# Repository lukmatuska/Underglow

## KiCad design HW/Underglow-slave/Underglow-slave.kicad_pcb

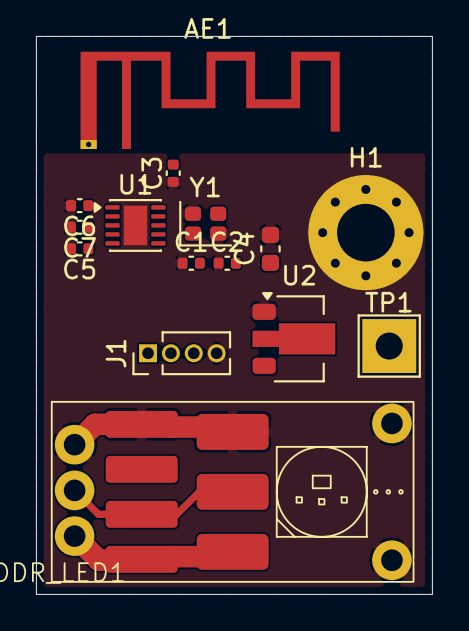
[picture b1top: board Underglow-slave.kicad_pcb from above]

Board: 2 copper layers, 22.0 x 31.0 mm, 15 parts (0 on the bottom side), 10 nets, no tracks yet.

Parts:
ADDR_LED1: Addressable_led_adapter_10mm
AE1: Antenna; Texas_SWRA117D_2.4GHz_Right
C1, C2, C3: DNP; C_0402_1005Metric
C4: 1u 25V; C_0603_1608Metric
C5: 1u; C_0402_1005Metric
C6: 2.2u; C_0402_1005Metric
C7: 100n; C_0402_1005Metric
H1: GND screw; MountingHole_3.2mm_M3_Pad_Via
J1: Debug_header; PinHeader_1x04_P1.27mm_Vertical
TP1: +12V in; TestPoint_THTPad_3.0x3.0mm_Drill1.5mm
U1: CH572Q; DFN-10-1EP_2.6x2.6mm_P0.5mm_EP1.3x2.2mm
U2: HT7550-1; SOT-89-3
Y1: 32MHz 8pF; Crystal_SMD_2016-4Pin_2.0x1.6mm

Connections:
+3.3V: C6.1, C7.1, J1.1, U1.1 (VDD33)
+5V: C5.1, U1.2 (V5), U2.3
+12V: ADDR_LED1.1 (VDD), C4.1, TP1.1, U2.2
/LED_RGB: ADDR_LED1.2 (DIN), U1.5 (PA7)
/SWCLK: J1.3, U1.4 (PA1)
/SWDIO: J1.2, U1.3 (PA0)
/XIN: C1.2, U1.9 (XI), Y1.1
/XOUT: C2.2, U1.8 (XO), Y1.3
GND: ADDR_LED1.3 (GND), AE1.2, C1.1, C2.1, C3.1, C4.2, C5.2, C6.2, C7.2, H1.1, J1.4, U1.11, U2.1, Y1.2, Y1.4
unnamed: AE1.1 (A_1), C3.2, U1.10 (ANT)
